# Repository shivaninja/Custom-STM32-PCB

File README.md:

# Custom STM32 PCB Board

A custom-designed STM32 development board built around the **STM32F103C8T6** microcontroller. The project includes the KiCad schematic, PCB layout, component 3D models, and design-review images.

## Project overview

This project is a custom PCB implementation of an STM32F103-based development board. It brings together the microcontroller, external clock circuit, USB connectivity, regulated 3.3 V power, reset/boot support, and breakout headers for external connections.

The board is intended as a hardware platform for embedded development and experimentation with the STM32F1 family.

## Main features

- **STM32F103C8Tx** microcontroller.
- External **16 MHz** crystal clock circuit.
- **Micro-USB** connector.
- **AMS1117-3.3** linear voltage regulator.
- USB data-line connections and supporting resistors.
- Reset and boot configuration circuitry.
- Breakout headers for power, UART, SWD, and general-purpose signals.
- Status LED and mounting holes.

The exact pin mapping and component values should be taken from the schematic.

## Hardware overview

| Component / circuit | Purpose |
|---|---|
| STM32F103C8Tx | Main 32-bit ARM Cortex-M3 microcontroller |
| 16 MHz crystal (Y2) | External high-speed clock source |
| AMS1117-3.3 (U2) | 3.3 V linear voltage regulation |
| Micro-USB connector (USB1) | USB connection and VBUS input |
| 4-pin headers (J1, J2, J3) | Breakout connections for power and signals |
| SW_SPDT (SW2) | Board configuration / switching |
| LED (D1) | Visual status indication |
| FB1 | Ferrite bead for supply filtering |
| Mounting holes (H1–H4) | Mechanical mounting |

## Design images

### Schematic

### PCB layout

**Front and back copper layers**

**Front copper**

**Back copper**

### 3D PCB views

## Schematic overview

The schematic is organized around these functional sections:

1. **Microcontroller:** STM32F103C8Tx with its power, ground, reset, and boot connections.
2. **Clock:** 16 MHz external crystal and associated load capacitors.
3. **Power:** USB VBUS input feeding the AMS1117-3.3 regulator, with decoupling and filtering components.
4. **USB:** Micro-USB connector and USB data-line connections.
5. **Debug and expansion:** Header connections for SWD, UART, power, and other signals.
6. **User interface:** LED and board configuration switch.

## Design rule checks

The supplied KiCad screenshots show the following results at the time they were captured:

| Check | Reported result |
|---|---:|
| Electrical Rules Checker (ERC) | 0 violations, 0 warnings |
| Design Rules Checker (DRC) | 0 violations, 0 unconnected items, 31 warnings |

The DRC screenshot also shows 5 ignored tests. These screenshots are a record of a particular design-check run, not a guarantee that the board is fabrication-ready. Review all warnings and rerun ERC/DRC with the intended fabrication constraints before manufacturing.

**ERC result**

**DRC result**

## Repository contents

```text
Custom-STM32-PCB/
├── STM32-Board.kicad_pro       # KiCad project
├── STM32-Board.kicad_sch       # Schematic
├── STM32-Board.kicad_pcb       # PCB layout
├── Schema-PDF/
│   └── STM32-Board.pdf         # Schematic exported as PDF
├── Pictures/
│   ├── Schema.png
│   ├── Front-Copper.png
│   ├── Back-Copper.png
│   ├── Front-&-Back-Copper.png
│   ├── Top-View.png
│   ├── Front-Diagnol.png
│   ├── Back Diagnol.png
│   ├── Bottom.png
│   ├── ERC.png
│   └── DRC.png
├── Micro-USB-Custom/           # Micro-USB connector 3D model
└── Piin_Header_3D_Model/       # Pin-header 3D model
```

## Opening the KiCad project

1. Install [KiCad](https://www.kicad.org/).
2. Clone or download this repository.
3. Open `STM32-Board.kicad_pro`.
4. Open the schematic or PCB editor to inspect or modify the design.
5. Keep the 3D model folders in their repository-relative locations so the board's 3D viewer can resolve the models.

If a 3D model is missing, review the model path in the footprint properties and update it to the correct local or project-relative path.

## Programming and development

The repository contains the hardware design files, but does not include firmware or a software project. To use the board in an embedded application, add firmware built with a suitable STM32 toolchain, such as STM32CubeIDE or an equivalent ARM embedded development environment.

The board exposes header connections intended for external signals and debugging. Confirm the actual header pinout in `STM32-Board.kicad_sch` before connecting a programmer, debugger, USB host, or peripheral.

## Important hardware notes

- Verify the USB input and regulator input/output ratings before powering the board.
- The AMS1117 is a linear regulator; check its thermal dissipation for the intended input voltage and load current.
- Confirm the USB data-line routing and the STM32 USB configuration against the intended firmware and USB use case.
- Check the board's connector pinout and voltage levels before connecting external hardware.
- Review the DRC warnings and fabrication constraints before ordering PCBs.
- Use appropriate ESD precautions when handling the assembled board.

## Project status

- [x] STM32F103-based schematic
- [x] Custom PCB layout
- [x] 3D board visualization
- [x] Schematic PDF export
- [x] ERC / DRC screenshots
- [ ] Firmware source code included
- [ ] Bring-up and hardware test results documented
- [ ] Manufacturing outputs (Gerbers and drill files) included

Update this checklist as the project progresses.

## License

No license file was included in the supplied archive. Add a `LICENSE` file to define how others may use, modify, and distribute this hardware design.

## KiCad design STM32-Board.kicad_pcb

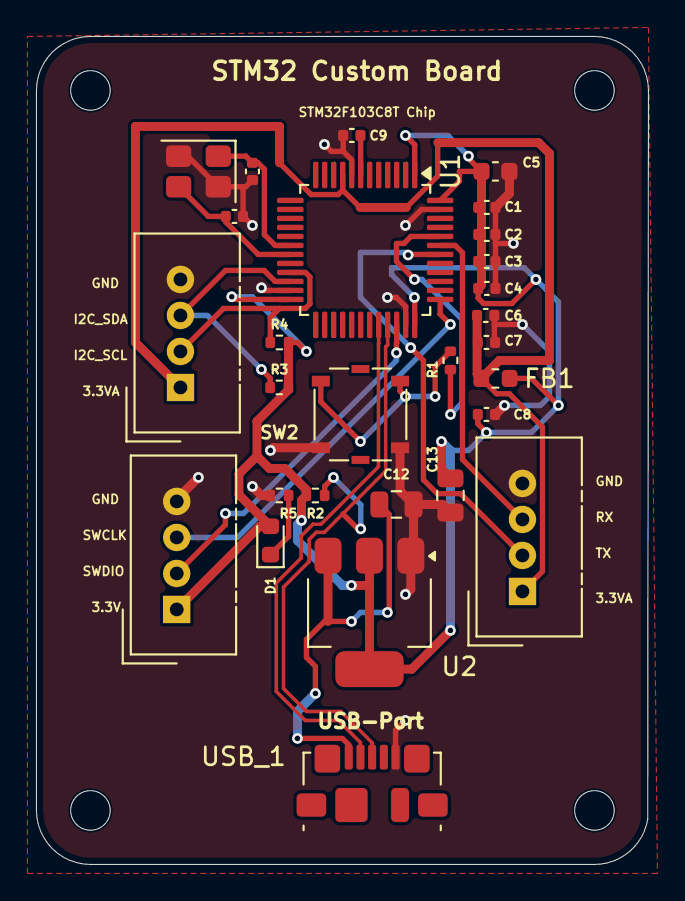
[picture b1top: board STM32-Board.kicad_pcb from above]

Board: 2 copper layers, 34.0 x 46.0 mm, 32 parts (0 on the bottom side), 18 nets.

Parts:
C1, C2, C3, C4, C9: 100n; C_0402_1005Metric
C5: 10u; C_0603_1608Metric
C6: 10n; C_0402_1005Metric
C7, C8: 1u; C_0402_1005Metric
C12, C13: 22u; C_0805_2012Metric
C14, C15: 10p; C_0402_1005Metric
D1: LED; LED_0603_1608Metric
FB1: 120R; L_0603_1608Metric
H1, H2, H3, H4: MountingHole; MountingHole_2.2mm_M2
J1, J2, J3: Conn_01x04_Pin; NS-Tech_Grove_1x04_P2mm_Vertical
R1: 10k; R_0402_1005Metric
R2, R3, R4, R5: 1.5K; R_0402_1005Metric
SW2: SW_SPDT; SW_SPST_Panasonic_EVQPL_3PL_5PL_PT_A08
U1: STM32F103C8Tx; LQFP-48_7x7mm_P0.5mm
U2: AMS1117-3.3; SOT-223-3_TabPin2
USB_1: USB_B_Micro; USB_Micro-B_Molex_47346-0001
Y2: 16MHz; Crystal_SMD_3225-4Pin_3.2x2.5mm

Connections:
+3.3V: C1.1, C2.1, C3.1, C4.1, C5.1, C8.1, C13.1, D1.2 (A), FB1.2, J3.1, R2.1, R3.2, R4.2, U1.1 (VBAT), U1.24 (VDD), U1.36 (VDD), U1.48 (VDD), U2.2 (VO)
+3.3VA: C6.1, C7.1, FB1.1, J1.1, J2.1, U1.9 (VDDA)
/I2C_SCL: J1.2, R4.1, U1.21 (PB10)
/I2C_SDA: J1.3, R3.1, U1.22 (PB11)
/NRST: C9.1, U1.7 (NRST)
/SWCLK: J3.3, U1.37 (PA14)
/SWDIO: J3.2, U1.34 (PA13)
/USB_D+: R2.2, U1.33 (PA12), USB_1.3 (D+)
/USB_D-: U1.32 (PA11), USB_1.2 (D-)
GND: C1.2, C2.2, C3.2, C4.2, C5.2, C6.2, C7.2, C8.2, C9.2, C12.2, C13.2, C14.2, C15.2, J1.4, J2.4, J3.4, R5.1, SW2.1 (A), U1.8 (VSSA), U1.23 (VSS), U1.35 (VSS), U1.47 (VSS), U2.1 (GND), USB_1.5 (GND), Y2.2 (G), Y2.4 (G)
HSE_IN: C14.1, U1.18 (PB0), Y2.1
HSE_OUT: C15.1, U1.19 (PB1), Y2.3
unnamed: D1.1 (K), R5.2
unnamed: R1.1, SW2.2 (B)
unnamed: R1.2, U1.44 (BOOT0)
UART_RX: J2.3, U1.43 (PB7)
UART_TX: J2.2, U1.42 (PB6)
VBUS: C12.1, U2.3 (VI), USB_1.1 (VBUS)
